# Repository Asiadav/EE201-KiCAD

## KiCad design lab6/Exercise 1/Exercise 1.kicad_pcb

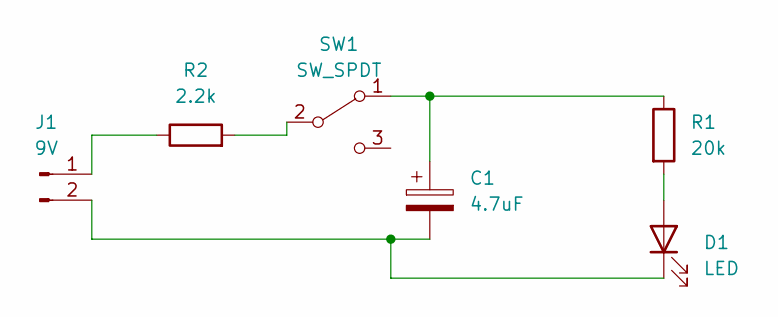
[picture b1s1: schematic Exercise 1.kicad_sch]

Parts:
C1: 4.7uF; C_Radial_D5.0mm_H5.0mm_P2.00mm
D1: LED; LED_D5.0mm
J1: 9V; JST_PH_B2B-PH-K_1x02_P2.00mm_Vertical
R1: 20k; R_Axial_DIN0516_L15.5mm_D5.0mm_P20.32mm_Horizontal
R2: 2.2k; R_Axial_DIN0516_L15.5mm_D5.0mm_P20.32mm_Horizontal
SW1: SW_SPDT; SW_E-Switch_EG1224_SPDT_Angled

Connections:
unnamed: C1.1, R1.1, SW1.1 (A)
unnamed: C1.2, D1.1 (K), J1.2
unnamed: D1.2 (A), R1.2
unnamed: J1.1, R2.1
unnamed: R2.2, SW1.2 (B)

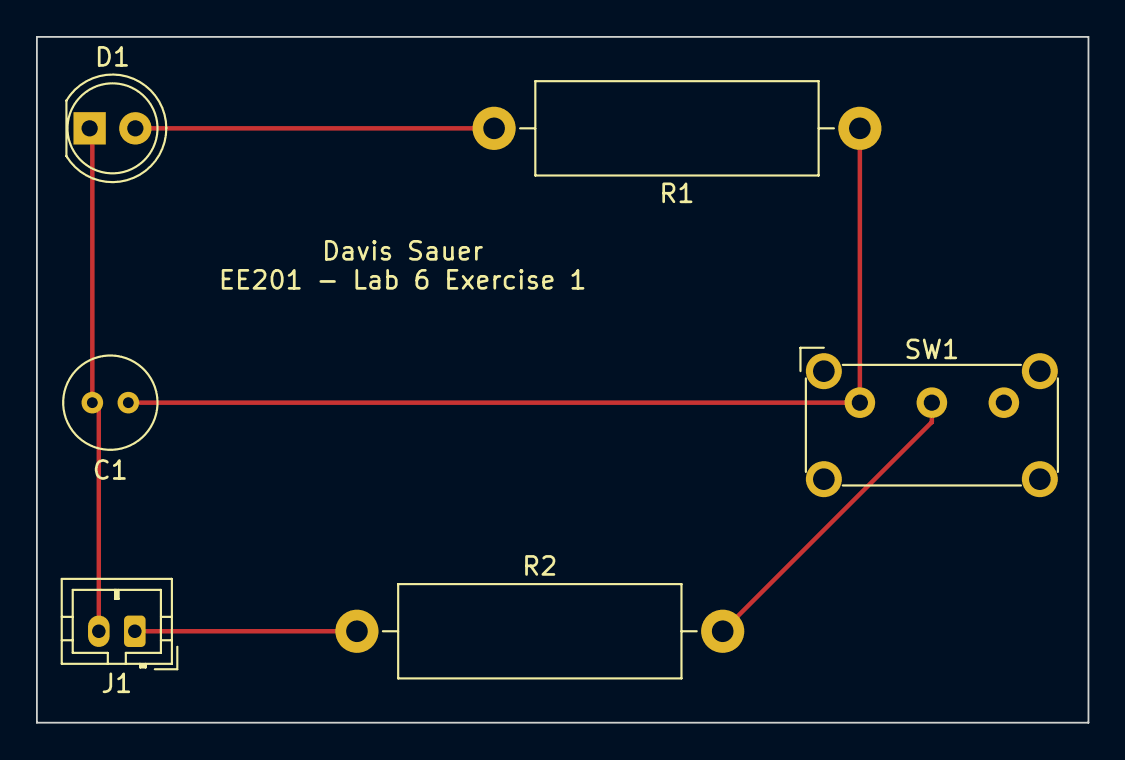
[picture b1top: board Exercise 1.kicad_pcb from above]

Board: 2 copper layers, 58.4 x 38.1 mm, 6 parts (0 on the bottom side), 5 nets.

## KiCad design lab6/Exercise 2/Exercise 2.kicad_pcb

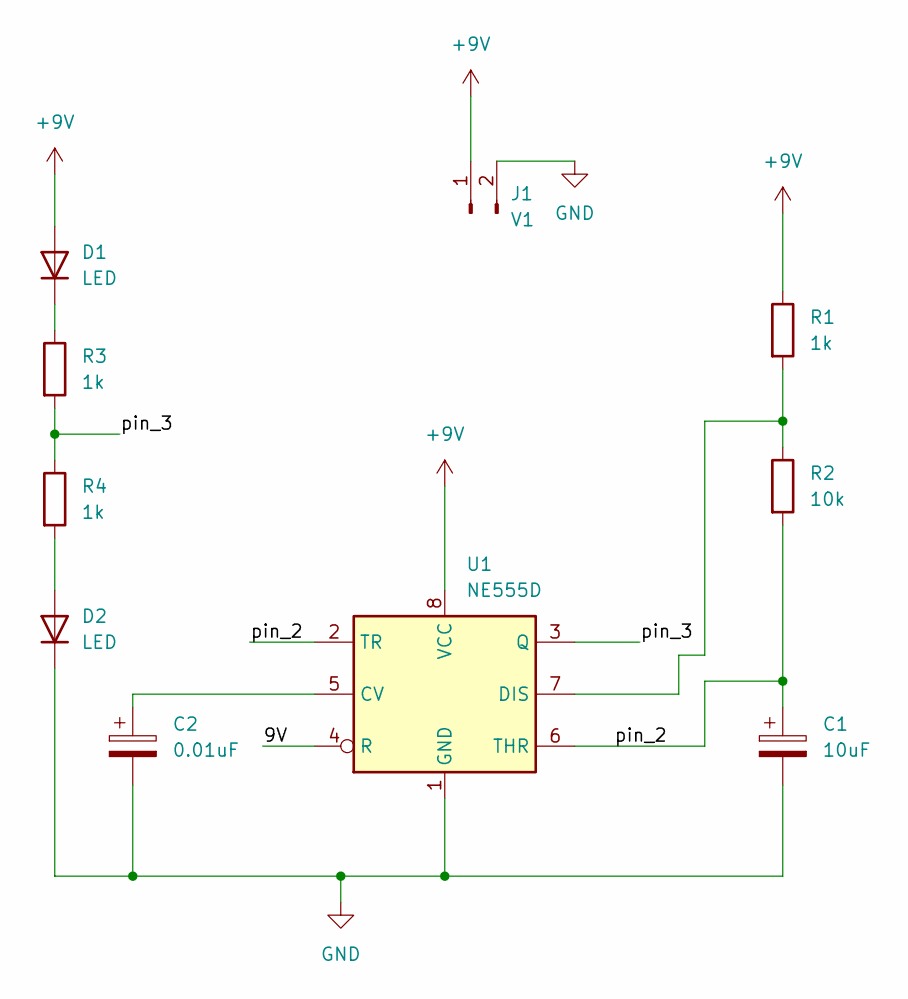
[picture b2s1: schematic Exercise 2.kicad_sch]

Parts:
C1: 10uF; CP_EIA-3216-18_Kemet-A_Pad1.58x1.35mm_HandSolder
C2: 0.01uF; C_0805_2012Metric_Pad1.18x1.45mm_HandSolder
D1, D2: LED; LED_1206_3216Metric_Pad1.42x1.75mm_HandSolder
J1: V1; TerminalBlock_bornier-2_P5.08mm
R1, R3, R4: 1k; R_0805_2012Metric_Pad1.20x1.40mm_HandSolder
R2: 10k; R_0805_2012Metric_Pad1.20x1.40mm_HandSolder
U1: NE555D; SOIC-8_3.9x4.9mm_P1.27mm

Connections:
+9V: D1.2 (A), J1.1, R1.1, U1.8 (VCC)
/9V: U1.4 (R)
/pin_2: C1.1, R2.2, U1.2 (TR), U1.6 (THR)
/pin_3: R3.2, R4.1, U1.3 (Q)
GND: C1.2, C2.2, D2.1 (K), J1.2, U1.1 (GND)
unnamed: C2.1, U1.5 (CV)
unnamed: D1.1 (K), R3.1
unnamed: D2.2 (A), R4.2
unnamed: R1.2, R2.1, U1.7 (DIS)

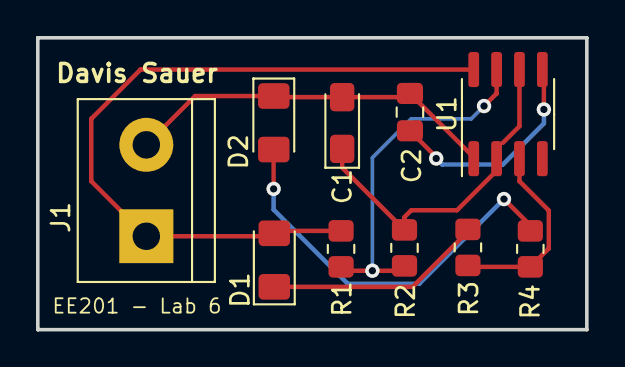
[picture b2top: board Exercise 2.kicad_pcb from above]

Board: 2 copper layers, 30.5 x 16.2 mm, 10 parts (0 on the bottom side), 8 nets.

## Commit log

2023-01-26 adding lab 4 files
2023-02-09 adding starting files
2023-02-09 lab 6 complete
2023-02-16 adding gerber files
